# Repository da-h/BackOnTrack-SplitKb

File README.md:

<h3 align="center">
    <br/>
    <br/><br/>
    Custom Split-Keyboard with 44 keys, 2 trackpads, 2 trackpad-buttons, per-key LED, underglow LED. Supports <a href="https://qmk.fm/">QMK Firmware</a>.
</h3>

<p align="center"> Steps: <a href="#setup">Manufacture</a>, <a href="#installation">Install</a>, <a href="#flashing">Flash</a>, <a href="#assemble">Assemble</a>
</p>

# Manufacture
(coming soon)

# Install
(coming soon)

# Flash
(coming soon)

# Assemble
(coming soon)

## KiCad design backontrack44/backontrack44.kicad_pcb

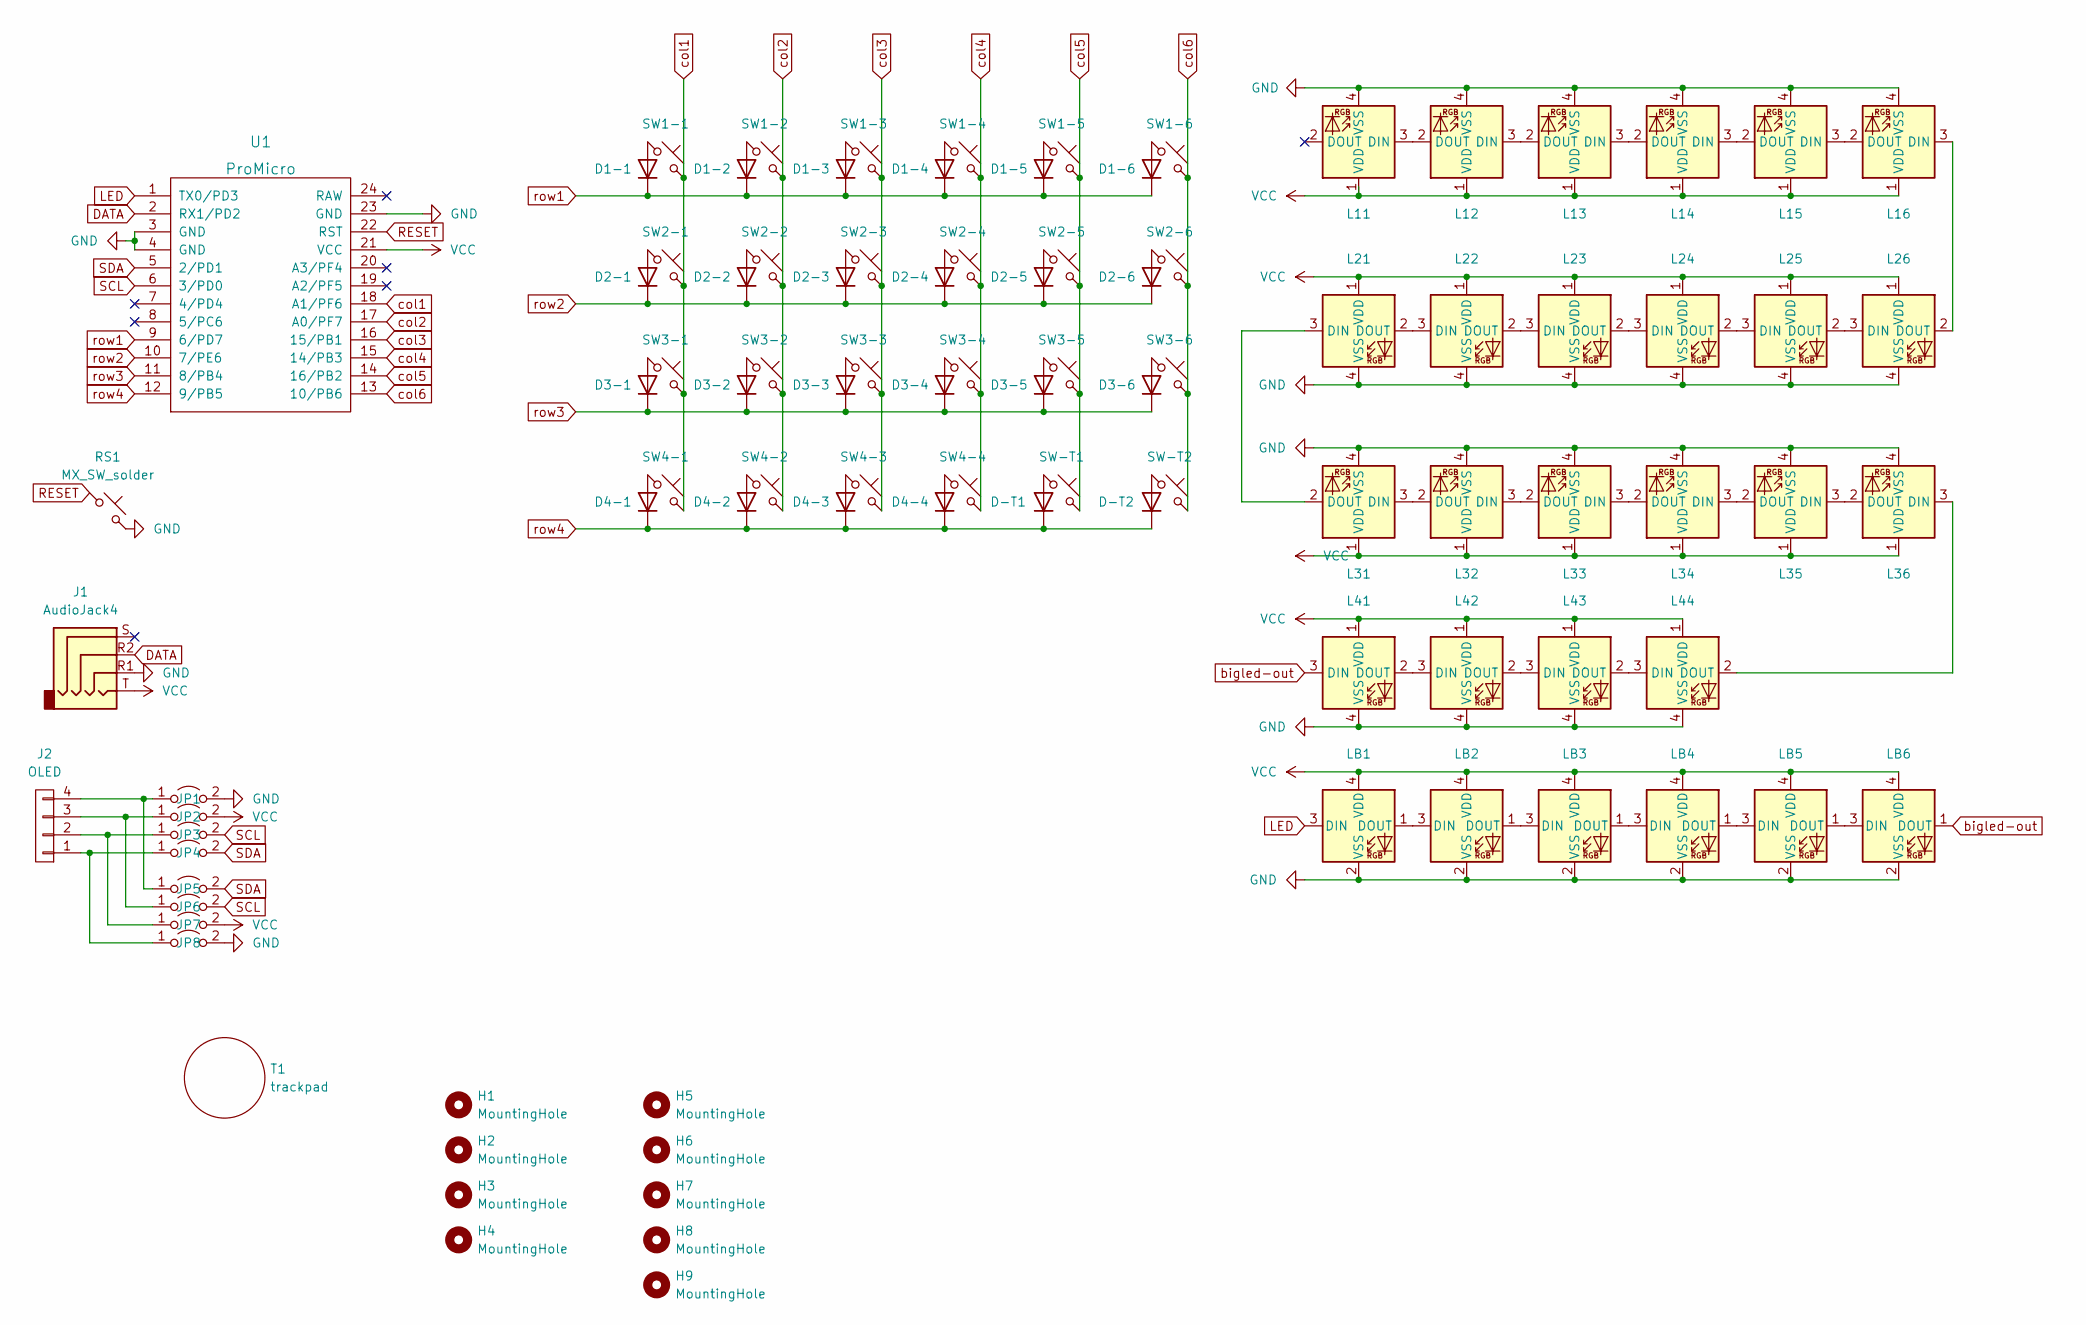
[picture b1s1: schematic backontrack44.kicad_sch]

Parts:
D1-1, D1-2, D1-3, D1-4, D1-5, D1-6, D2-1, D2-2, D2-3, D2-4, D2-5, D2-6, D3-1, D3-2, D3-3, D3-4, D3-5, D3-6, D4-1, D4-2, D4-3, D4-4: 1N4148W; Diode_SOD123
D-T1, D-T2: 1N4148W; Diode_SOD123
H1, H2, H3, H4: MountingHole; MountingHole_2.2mm_M2_ISO14580_Pad
H5, H6, H7, H8, H9: MountingHole; MountingHole_2.5mm_Pad
J1: AudioJack4; TRRS_JACK_MJ4PP9_Renamed
J2: OLED; OLED_4Pin
JP1, JP2, JP3, JP4, JP5, JP6, JP7, JP8: Jumper_2_Open; Jumper
L11, L12, L13, L14, L15, L16, L31, L32, L33, L34, L35, L36: choc_SK6812MINI-E; LED_choc_6028R_doublesided_rotated
L21, L22, L23, L24, L25, L26, L41, L42, L43, L44: choc_SK6812MINI-E; LED_choc_6028R_doublesided_rotated_twice
LB1, LB2, LB3, LB4, LB5, LB6: SK6812MINI; LED_SK6812MINI_PLCC4_3.5x3.5mm_P1.75mm
RS1: MX_SW_solder; TACT_SWITCH_TVBP06
SW1-1, SW1-2, SW1-3, SW1-4, SW1-5, SW1-6, SW2-1, SW2-2, SW2-3, SW2-4, SW2-5, SW2-6, SW3-1, SW3-2, SW3-3, SW3-4, SW3-5, SW3-6, SW4-2, SW4-3, SW4-4: choc_SW_HS; SW_choc_HS_1u_reversible_rotated
SW4-1: choc_SW_HS; SW_choc_HS_1.5u_reversible_rotated
SW-T1, SW-T2: choc_SW_HS; SW_PUSH_6mm_H5mm
T1: trackpad; trackpad_35mm
U1: ProMicro; ProMicro_rev2

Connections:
DATA: J1.R2, U1.2 (RX1/PD2)
GND: J1.R1, JP1.2 (B), JP8.2 (B), L11.4 (VSS), L12.4 (VSS), L13.4 (VSS), L14.4 (VSS), L15.4 (VSS), L16.4 (VSS), L21.4 (VSS), L22.4 (VSS), L23.4 (VSS), L24.4 (VSS), L25.4 (VSS), L26.4 (VSS), L31.4 (VSS), L32.4 (VSS), L33.4 (VSS), L34.4 (VSS), L35.4 (VSS), L36.4 (VSS), L41.4 (VSS), L42.4 (VSS), L43.4 (VSS), L44.4 (VSS), LB1.2 (VSS), LB2.2 (VSS), LB3.2 (VSS), LB4.2 (VSS), LB5.2 (VSS), LB6.2 (VSS), RS1.2, U1.3 (GND), U1.4 (GND), U1.23 (GND)
LED: LB1.3 (DIN), U1.1 (TX0/PD3)
unnamed: D1-1.2 (A), SW1-1.1
unnamed: D1-2.2 (A), SW1-2.1
unnamed: D1-3.2 (A), SW1-3.1
unnamed: D1-4.2 (A), SW1-4.1
unnamed: D1-5.2 (A), SW1-5.1
unnamed: D1-6.2 (A), SW1-6.1
unnamed: D2-1.2 (A), SW2-1.1
unnamed: D2-2.2 (A), SW2-2.1
unnamed: D2-3.2 (A), SW2-3.1
unnamed: D2-4.2 (A), SW2-4.1
unnamed: D2-5.2 (A), SW2-5.1
unnamed: D2-6.2 (A), SW2-6.1
unnamed: D3-1.2 (A), SW3-1.1
unnamed: D3-2.2 (A), SW3-2.1
unnamed: D3-3.2 (A), SW3-3.1
unnamed: D3-4.2 (A), SW3-4.1
unnamed: D3-5.2 (A), SW3-5.1
unnamed: D3-6.2 (A), SW3-6.1
unnamed: D4-1.2 (A), SW4-1.1
unnamed: D4-2.2 (A), SW4-2.1
unnamed: D4-3.2 (A), SW4-3.1
unnamed: D4-4.2 (A), SW4-4.1
unnamed: D-T1.2 (A), SW-T1.1
unnamed: D-T2.2 (A), SW-T2.1
unnamed: J2.1, JP4.1 (A), JP8.1 (A)
unnamed: J2.2, JP3.1 (A), JP7.1 (A)
unnamed: J2.3, JP2.1 (A), JP6.1 (A)
unnamed: J2.4, JP1.1 (A), JP5.1 (A)
unnamed: L11.3 (DIN), L12.2 (DOUT)
unnamed: L12.3 (DIN), L13.2 (DOUT)
unnamed: L13.3 (DIN), L14.2 (DOUT)
unnamed: L14.3 (DIN), L15.2 (DOUT)
unnamed: L15.3 (DIN), L16.2 (DOUT)
unnamed: L16.3 (DIN), L26.2 (DOUT)
unnamed: L21.2 (DOUT), L22.3 (DIN)
unnamed: L21.3 (DIN), L31.2 (DOUT)
unnamed: L22.2 (DOUT), L23.3 (DIN)
unnamed: L23.2 (DOUT), L24.3 (DIN)
unnamed: L24.2 (DOUT), L25.3 (DIN)
unnamed: L25.2 (DOUT), L26.3 (DIN)
unnamed: L31.3 (DIN), L32.2 (DOUT)
unnamed: L32.3 (DIN), L33.2 (DOUT)
unnamed: L33.3 (DIN), L34.2 (DOUT)
unnamed: L34.3 (DIN), L35.2 (DOUT)
unnamed: L35.3 (DIN), L36.2 (DOUT)
unnamed: L36.3 (DIN), L44.2 (DOUT)
unnamed: L41.2 (DOUT), L42.3 (DIN)
unnamed: L42.2 (DOUT), L43.3 (DIN)
unnamed: L43.2 (DOUT), L44.3 (DIN)
unnamed: LB1.1 (DOUT), LB2.3 (DIN)
unnamed: LB2.1 (DOUT), LB3.3 (DIN)
unnamed: LB3.1 (DOUT), LB4.3 (DIN)
unnamed: LB4.1 (DOUT), LB5.3 (DIN)
unnamed: LB5.1 (DOUT), LB6.3 (DIN)
RESET: RS1.1, U1.22 (RST)
SCL: JP3.2 (B), JP6.2 (B), U1.6 (3/PD0)
SDA: JP4.2 (B), JP5.2 (B), U1.5 (2/PD1)
VCC: J1.T, JP2.2 (B), JP7.2 (B), L11.1 (VDD), L12.1 (VDD), L13.1 (VDD), L14.1 (VDD), L15.1 (VDD), L16.1 (VDD), L21.1 (VDD), L22.1 (VDD), L23.1 (VDD), L24.1 (VDD), L25.1 (VDD), L26.1 (VDD), L31.1 (VDD), L32.1 (VDD), L33.1 (VDD), L34.1 (VDD), L35.1 (VDD), L36.1 (VDD), L41.1 (VDD), L42.1 (VDD), L43.1 (VDD), L44.1 (VDD), LB1.4 (VDD), LB2.4 (VDD), LB3.4 (VDD), LB4.4 (VDD), LB5.4 (VDD), LB6.4 (VDD), U1.21 (VCC)
bigled-out: L41.3 (DIN), LB6.1 (DOUT)
col1: SW1-1.2, SW2-1.2, SW3-1.2, SW4-1.2, U1.18 (A1/PF6)
col2: SW1-2.2, SW2-2.2, SW3-2.2, SW4-2.2, U1.17 (A0/PF7)
col3: SW1-3.2, SW2-3.2, SW3-3.2, SW4-3.2, U1.16 (15/PB1)
col4: SW1-4.2, SW2-4.2, SW3-4.2, SW4-4.2, U1.15 (14/PB3)
col5: SW1-5.2, SW2-5.2, SW3-5.2, SW-T1.2, U1.14 (16/PB2)
col6: SW1-6.2, SW2-6.2, SW3-6.2, SW-T2.2, U1.13 (10/PB6)
row1: D1-1.1 (K), D1-2.1 (K), D1-3.1 (K), D1-4.1 (K), D1-5.1 (K), D1-6.1 (K), U1.9 (6/PD7)
row2: D2-1.1 (K), D2-2.1 (K), D2-3.1 (K), D2-4.1 (K), D2-5.1 (K), D2-6.1 (K), U1.10 (7/PE6)
row3: D3-1.1 (K), D3-2.1 (K), D3-3.1 (K), D3-4.1 (K), D3-5.1 (K), D3-6.1 (K), U1.11 (8/PB4)
row4: D4-1.1 (K), D4-2.1 (K), D4-3.1 (K), D4-4.1 (K), D-T1.1 (K), D-T2.1 (K), U1.12 (9/PB5)

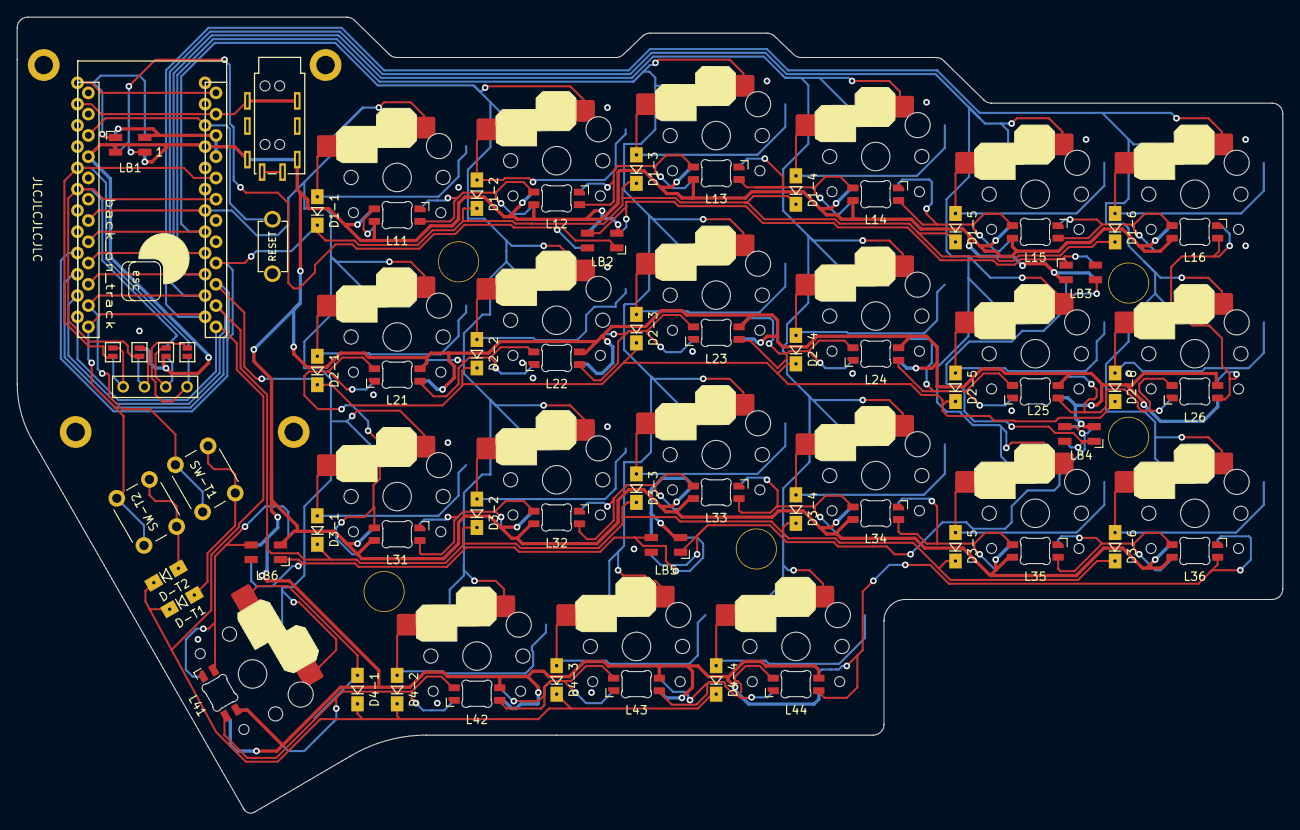
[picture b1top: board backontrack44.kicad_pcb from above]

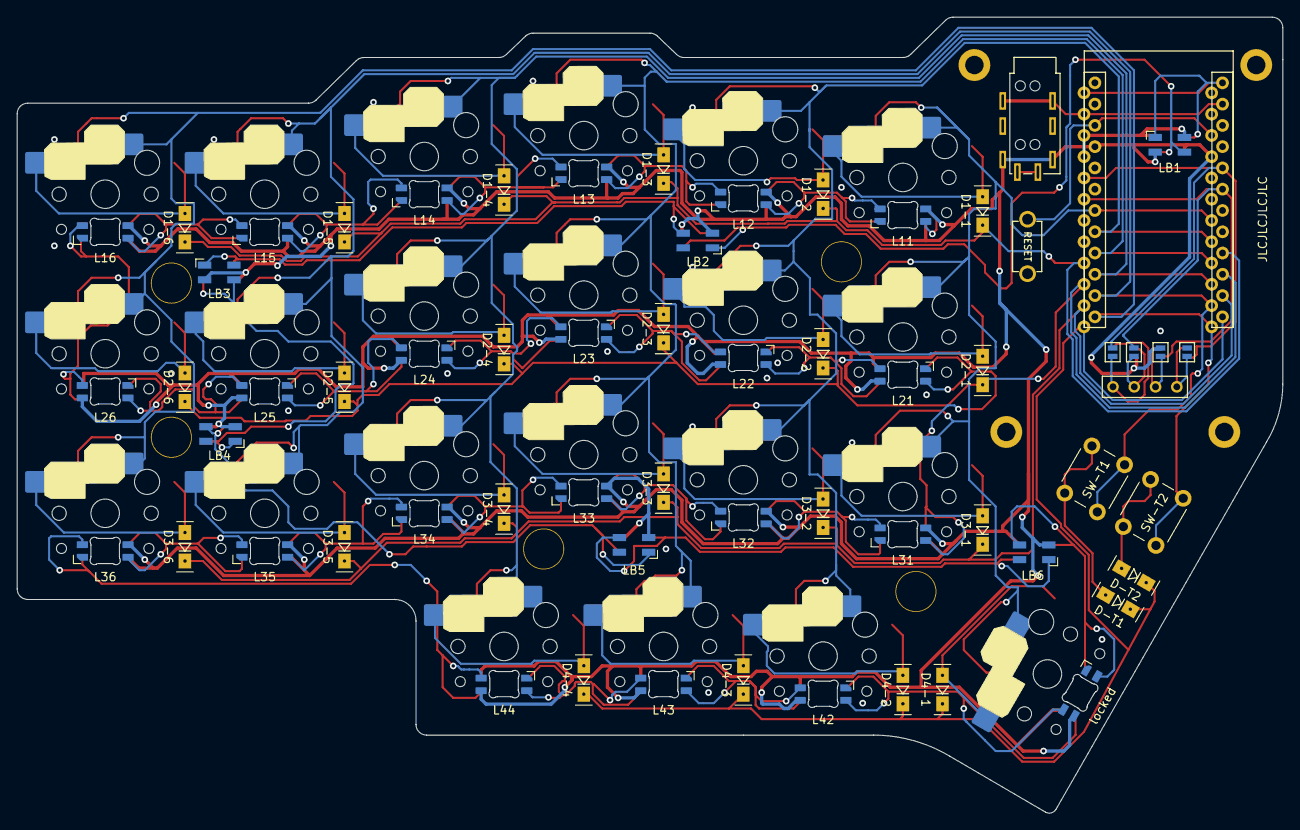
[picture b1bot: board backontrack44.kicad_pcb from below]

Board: 2 copper layers, 151.1 x 95.0 mm, 100 parts (4 on the bottom side), 72 nets.

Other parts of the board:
JLCJLCJLCJLC: production label
esc: Logo

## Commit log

2023-01-02 added footprints
2023-01-02 added gitignore for kicad projects
2023-01-02 added libraries
2023-01-02 added project files
2023-01-02 better fitting of the board on the right side
2023-01-02 fix overlapping errors
2023-01-02 fixed many DRC errors
2023-01-02 removed col5 and col6 loops
2023-01-02 fixed another DRC error
2023-01-05 added B-leds to back side as well
2023-01-05 added missing "true" connections
2023-01-05 fixed some missing GND connections
2023-01-05 fixed all missing GND connections
2023-01-05 simplified GND connections using VIAs
2023-01-05 tighter edge cuts
2023-01-05 simplified some connections
2023-01-05 added logo
2023-01-05 fixed most warnings
2023-01-05 fix last silkscreen warning
2023-01-05 final save
2023-01-05 moved holes away from b-leds
2023-06-19 renamed backontrack44-subfolder -> kicad
2023-06-19 added logo
    Update README.md
